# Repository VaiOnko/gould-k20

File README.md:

# gould-k20

This probe is tested and works well according to my test without knowing how the proper thing operates,

This is my project to create a reproduction state mode probe for the Gould K20 logic analyzer and document the unit.

I did not get any probes with the unit, so I had to create my own one from scratch. 
The probe contains logic to route the three clock inputs to any combination of the three clocks on the analyzer. They can also be inverted and ORred together. All this is configured from the unit itself in the menu pictured in menu4.jpg, and sent to a pair of shift registers in the probe. 

The probe connects to the main unit with a 34-pin ribbon cable. I use a PC floppy cable from which I removed the twist. 

The probe should work just like the original state mode probe, but I cannot be sure as I don't know anything about the original one.
The machine also came with an 8-channel timing mode probe. From what I understand, it had a configurable clock generator inside and thus would be quite difficult to recreate. 

The directory "logicanalyzer" contains the KiCad project for the probe. 
The directory "pictures" contains detailed pictures of the unit.
The directory "ROMs" contains dumps from all the ROMs in the system.

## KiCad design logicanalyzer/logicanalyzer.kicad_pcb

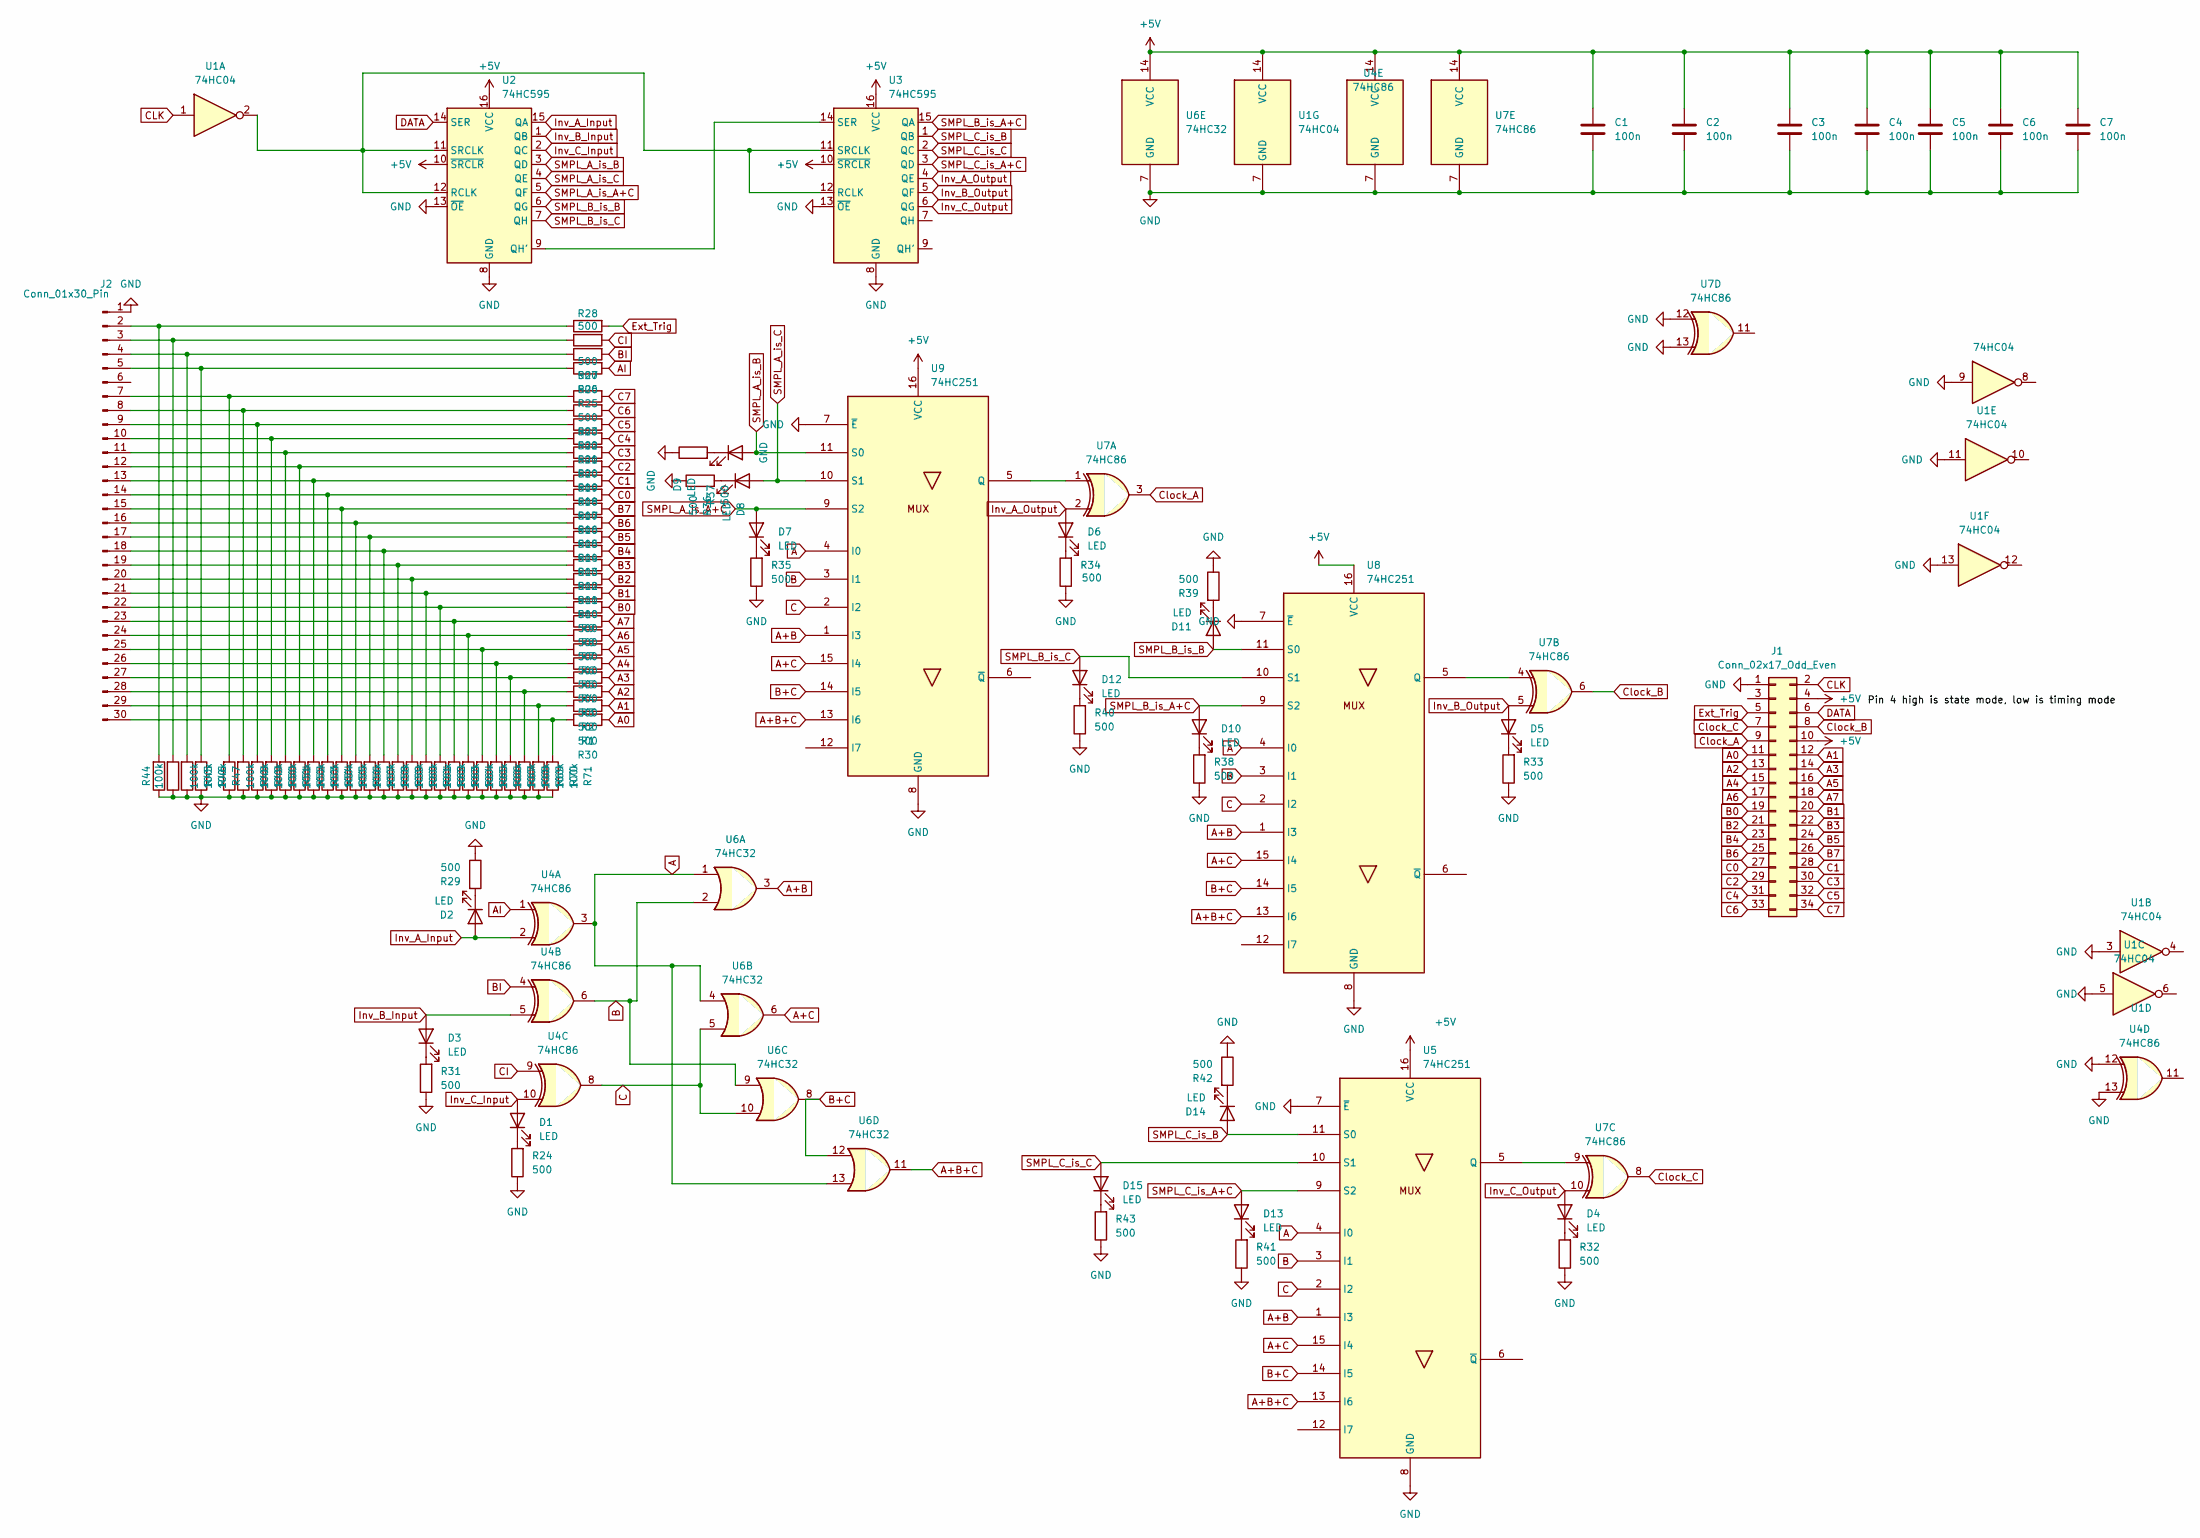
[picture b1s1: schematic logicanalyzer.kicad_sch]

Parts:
C1, C2, C3, C4, C5, C6, C7: 100n; C_0603_1608Metric
D1, D2, D3, D4, D5, D6, D7, D8, D9, D10, D11, D12, D13, D14, D15: LED; LED_0603_1608Metric
J1: Conn_02x17_Odd_Even; IDC-Header_2x17_P2.54mm_Vertical
J2: Conn_01x30_Pin; PinHeader_1x30_P2.54mm_Vertical
R1, R2, R3, R4, R5, R6, R7, R8, R9, R10, R11, R12, R13, R14, R15, R16, R17, R18, R19, R20, R21, R22, R23, R24, R25, R26, R27, R28, R29, R30, R31, R32, R33, R34, R35, R36, R37, R38, R39, R40, R41, R42, R43: 500; R_0603_1608Metric
R44, R45, R46, R47, R48, R49, R50, R51, R52, R53, R54, R55, R56, R57, R58, R59, R60, R61, R62, R63, R64, R65, R66, R67, R68, R69, R70, R71: 100k; R_0603_1608Metric
U1: 74HC04; SOIC-14_3.9x8.7mm_P1.27mm
U2, U3: 74HC595; SOIC-16_3.9x9.9mm_P1.27mm
U4, U7: 74HC86; SOIC-14_3.9x8.7mm_P1.27mm
U5, U8, U9: 74HC251; SOIC-16_3.9x9.9mm_P1.27mm
U6: 74HC32; SOIC-14_3.9x8.7mm_P1.27mm

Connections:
+5V: C1.1, C2.1, C3.1, C4.1, C5.1, C6.1, C7.1, J1.4, J1.10, U1.14 (VCC), U2.10 (~SRCLR), U2.16 (VCC), U3.10 (~SRCLR), U3.16 (VCC), U4.14 (VCC), U5.16 (VCC), U6.14 (VCC), U7.14 (VCC), U8.16 (VCC), U9.16 (VCC)
A: U4.3, U5.4 (I0), U6.1, U6.4, U6.13, U8.4 (I0), U9.4 (I0)
A0: J1.11, R30.2
A1: J1.12, R1.2
A2: J1.13, R2.2
A3: J1.14, R3.2
A4: J1.15, R4.2
A5: J1.16, R5.2
A6: J1.17, R6.2
A7: J1.18, R7.2
A+B: U5.1 (I3), U6.3, U8.1 (I3), U9.1 (I3)
A+B+C: U5.13 (I6), U6.11, U8.13 (I6), U9.13 (I6)
A+C: U5.15 (I4), U6.6, U8.15 (I4), U9.15 (I4)
AI: R25.2, U4.1
B: U4.6, U5.3 (I1), U6.2, U6.9, U8.3 (I1), U9.3 (I1)
B0: J1.19, R8.2
B1: J1.20, R9.2
B2: J1.21, R10.2
B3: J1.22, R11.2
B4: J1.23, R12.2
B5: J1.24, R13.2
B6: J1.25, R14.2
B7: J1.26, R15.2
B+C: U5.14 (I5), U6.8, U6.12, U8.14 (I5), U9.14 (I5)
BI: R26.2, U4.4
C: U4.8, U5.2 (I2), U6.5, U6.10, U8.2 (I2), U9.2 (I2)
C0: J1.27, R16.2
C1: J1.28, R17.2
C2: J1.29, R18.2
C3: J1.30, R19.2
C4: J1.31, R20.2
C5: J1.32, R21.2
C6: J1.33, R22.2
C7: J1.34, R23.2
CI: R27.2, U4.9
CLK: J1.2, U1.1
Clock_A: J1.9, U7.3
Clock_B: J1.8, U7.6
Clock_C: J1.7, U7.8
DATA: J1.6, U2.14 (SER)
Ext_Trig: J1.5, R28.2
GND: C1.2, C2.2, C3.2, C4.2, C5.2, C6.2, C7.2, J1.1, J2.1, R24.1, R29.1, R31.1, R32.1, R33.1, R34.1, R35.1, R36.1, R37.1, R38.1, R39.1, R40.1, R41.1, R42.1, R43.1, R44.1, R45.1, R46.1, R47.1, R48.1, R49.1, R50.1, R51.1, R52.1, R53.1, R54.1, R55.1, R56.1, R57.1, R58.1, R59.1, R60.1, R61.1, R62.1, R63.1, R64.1, R65.1, R66.1, R67.1, R68.1, R69.1, R70.1, R71.1, U1.3, U1.5, U1.7 (GND), U1.9, U1.11, U1.13, U2.8 (GND), U2.13 (~OE), U3.8 (GND), U3.13 (~OE), U4.7 (GND), U4.12, U4.13, U5.7 (~E), U5.8 (GND), U6.7 (GND), U7.7 (GND), U7.12, U7.13, U8.7 (~E), U8.8 (GND), U9.7 (~E), U9.8 (GND)
Inv_A_Input: D2.2 (A), U2.15 (QA), U4.2
Inv_A_Output: D6.2 (A), U3.4 (QE), U7.2
Inv_B_Input: D3.2 (A), U2.1 (QB), U4.5
Inv_B_Output: D5.2 (A), U3.5 (QF), U7.5
Inv_C_Input: D1.2 (A), U2.2 (QC), U4.10
Inv_C_Output: D4.2 (A), U3.6 (QG), U7.10
unnamed: D1.1 (K), R24.2
unnamed: D2.1 (K), R29.2
unnamed: D3.1 (K), R31.2
unnamed: D4.1 (K), R32.2
unnamed: D5.1 (K), R33.2
unnamed: D6.1 (K), R34.2
unnamed: D7.1 (K), R35.2
unnamed: D8.1 (K), R36.2
unnamed: D9.1 (K), R37.2
unnamed: D10.1 (K), R38.2
unnamed: D11.1 (K), R39.2
unnamed: D12.1 (K), R40.2
unnamed: D13.1 (K), R41.2
unnamed: D14.1 (K), R42.2
unnamed: D15.1 (K), R43.2
unnamed: J2.2, R28.1, R44.2
unnamed: J2.3, R27.1, R45.2
unnamed: J2.4, R26.1, R46.2
unnamed: J2.5, R25.1, R47.2
unnamed: J2.7, R23.1, R48.2
unnamed: J2.8, R22.1, R49.2
unnamed: J2.9, R21.1, R50.2
unnamed: J2.10, R20.1, R51.2
unnamed: J2.11, R19.1, R52.2
unnamed: J2.12, R18.1, R53.2
unnamed: J2.13, R17.1, R54.2
unnamed: J2.14, R16.1, R55.2
unnamed: J2.15, R15.1, R56.2
unnamed: J2.16, R14.1, R57.2
unnamed: J2.17, R13.1, R58.2
unnamed: J2.18, R12.1, R59.2
unnamed: J2.19, R11.1, R60.2
unnamed: J2.20, R10.1, R61.2
unnamed: J2.21, R9.1, R62.2
unnamed: J2.22, R8.1, R63.2
unnamed: J2.23, R7.1, R64.2
unnamed: J2.24, R6.1, R65.2
unnamed: J2.25, R5.1, R66.2
unnamed: J2.26, R4.1, R67.2
unnamed: J2.27, R3.1, R68.2
unnamed: J2.28, R2.1, R69.2
unnamed: J2.29, R1.1, R70.2
unnamed: J2.30, R30.1, R71.2
unnamed: U2.9 (QH'), U3.14 (SER)
unnamed: U1.2, U2.11 (SRCLK), U2.12 (RCLK), U3.11 (SRCLK), U3.12 (RCLK)
unnamed: U5.5 (Q), U7.9
unnamed: U7.4, U8.5 (Q)
unnamed: U7.1, U9.5 (Q)
SMPL_A_is_A+C: D7.2 (A), U2.5 (QF), U9.9 (S2)
SMPL_A_is_B: D9.2 (A), U2.3 (QD), U9.11 (S0)
SMPL_A_is_C: D8.2 (A), U2.4 (QE), U9.10 (S1)
SMPL_B_is_A+C: D10.2 (A), U3.15 (QA), U8.9 (S2)
SMPL_B_is_B: D11.2 (A), U2.6 (QG), U8.11 (S0)
SMPL_B_is_C: D12.2 (A), U2.7 (QH), U8.10 (S1)
SMPL_C_is_A+C: D13.2 (A), U3.3 (QD), U5.9 (S2)
SMPL_C_is_B: D14.2 (A), U3.1 (QB), U5.11 (S0)
SMPL_C_is_C: D15.2 (A), U3.2 (QC), U5.10 (S1)

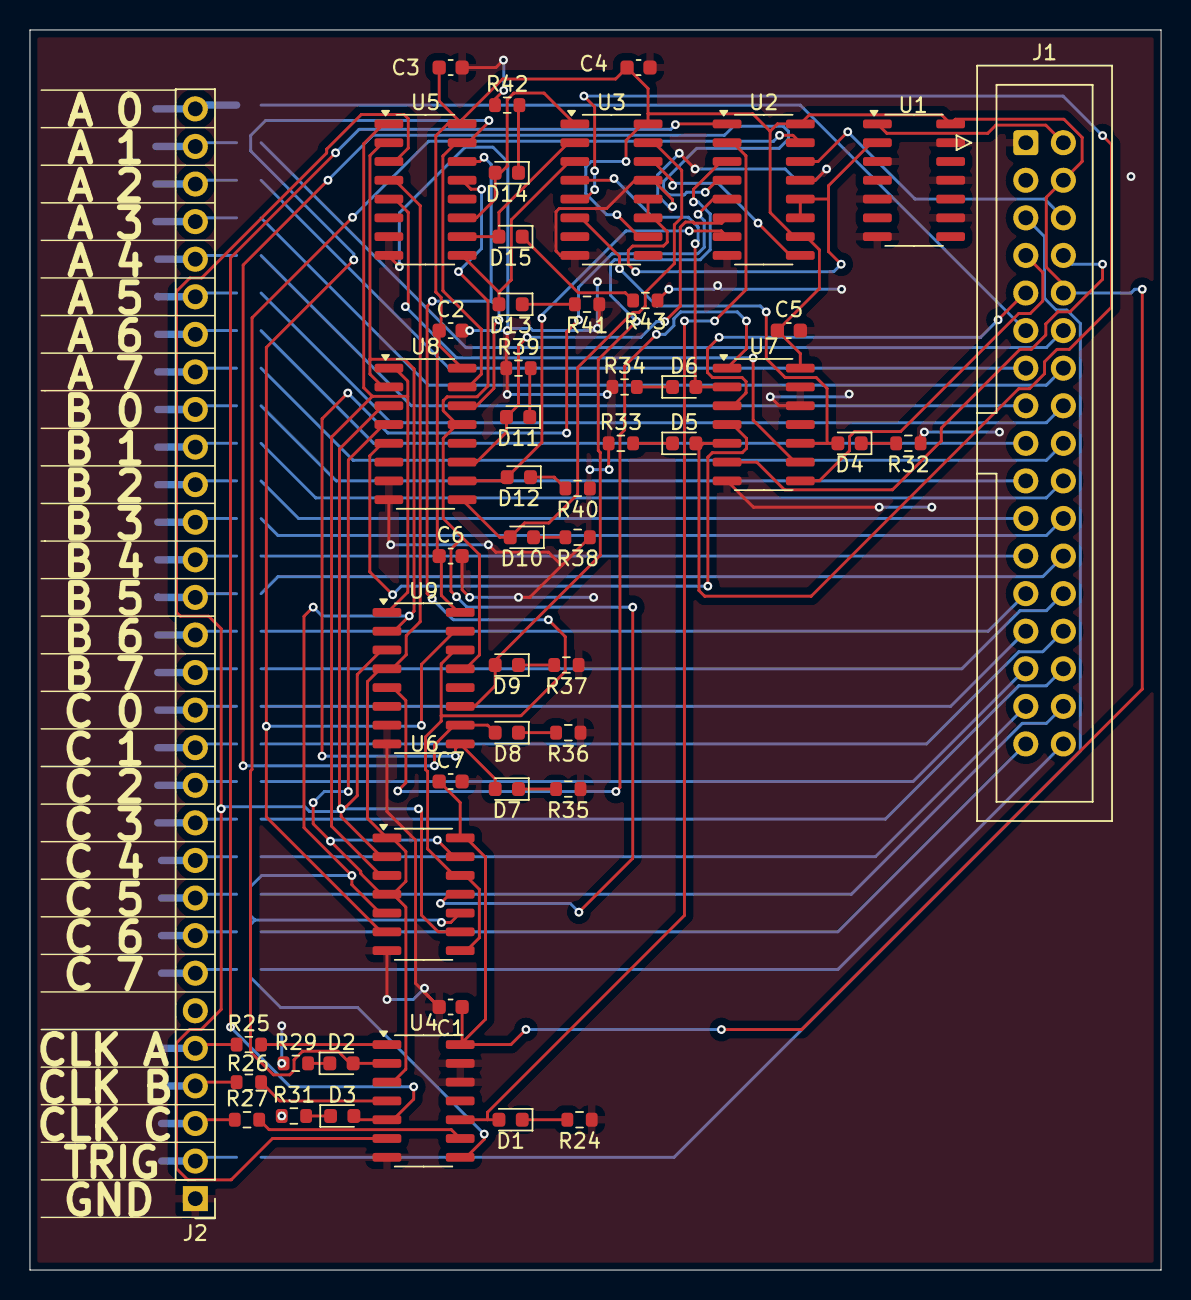
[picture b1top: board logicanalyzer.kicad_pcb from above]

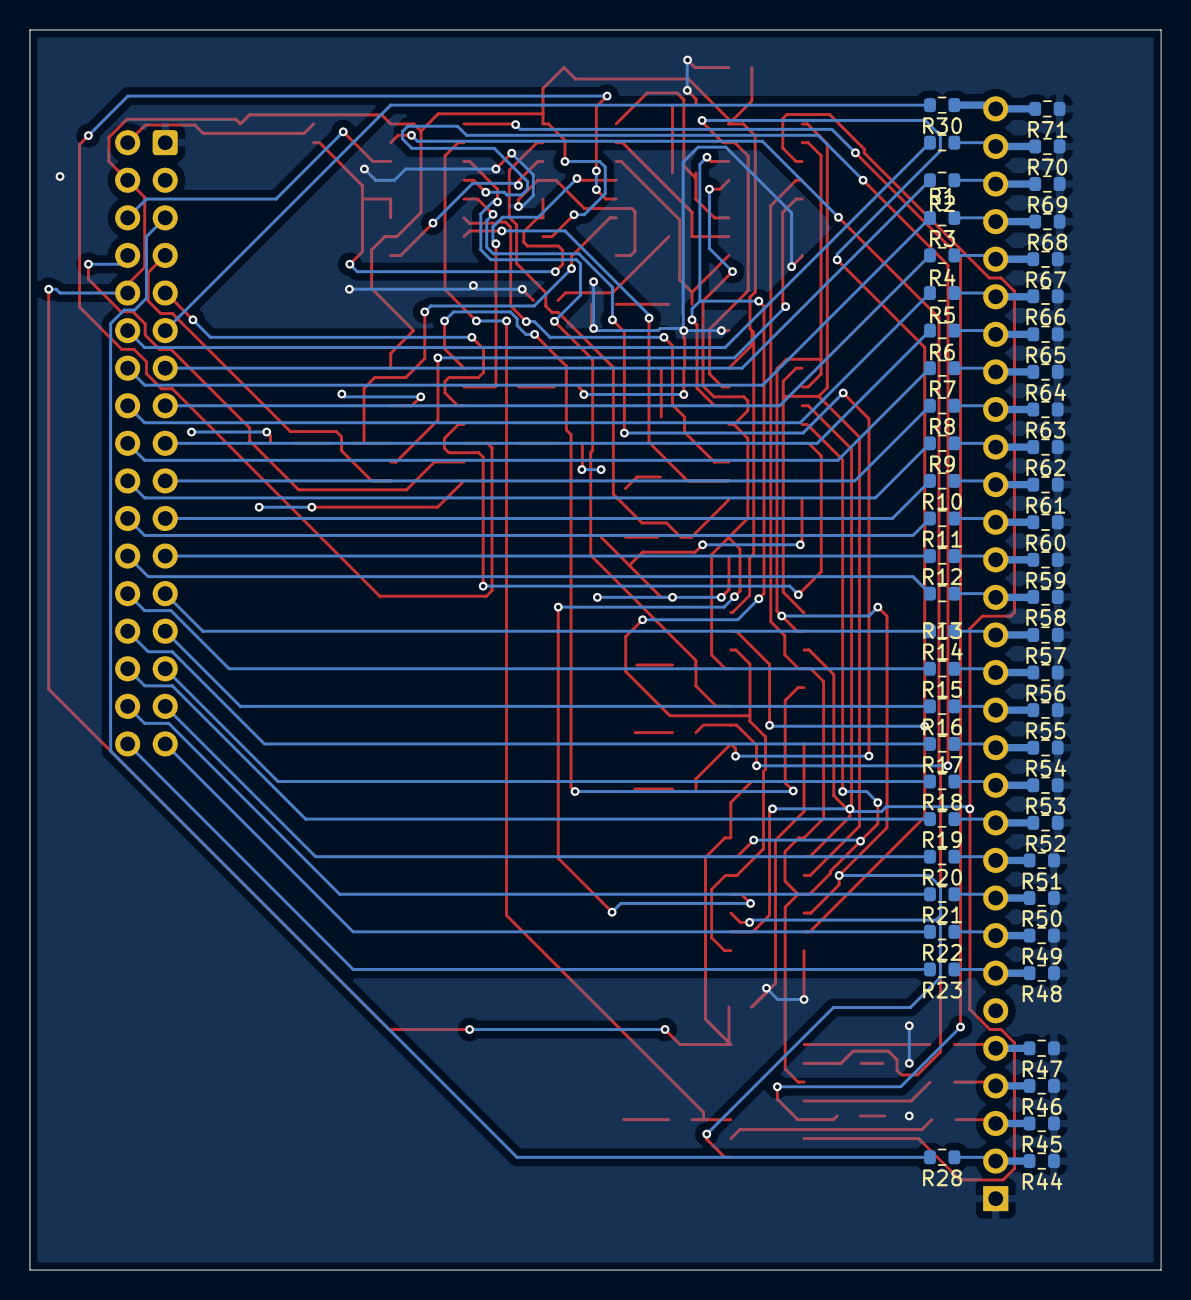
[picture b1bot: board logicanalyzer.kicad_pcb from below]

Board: 2 copper layers, 76.5 x 83.8 mm, 104 parts (53 on the bottom side), 105 nets.

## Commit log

2024-12-04 Add text to README
2024-12-04 Add KiCad project
2024-12-04 Add pictures
2024-12-04 Schematic changes
2024-12-04 Schematic change + typo in README
2024-12-06 Finalized PCB, added gerbers and pdf schematic
2025-01-07 Add ROM dumps
2025-01-07 Character ROM dump fixed
2025-08-15 Added picture and info about probe being tested
